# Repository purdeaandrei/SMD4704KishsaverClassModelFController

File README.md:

# SMD Model F controller based on TH Xwhatsit design. ('kishsaver' variant)

This variant is for IBM 4704 keyboards, aka 'kishsaver' class model F keyboards, like F107, F50, F62, F77
This variant is not 100% compatible with the https://www.modelfkeyboards.com/ recreations of the F62/F77, because the pin pitch is different,
although it is electrically compatible with those too, if one decides to wire it up with individual wires.

For other variants see:
* https://github.com/purdeaandrei/SMDModelFController/tree/extra_columns
* https://github.com/purdeaandrei/SMDModelFController
* https://github.com/listofoptions/TH-XWhatsIt

## Images

## Origins and license

This project is based on the Through-hole xwhatsit by listofoptions, which is un turn
based on the capsense controllers by XWhatsIt
(Tom Wong-Cornall). original liscencure holds, as well as CERN OSH
(compatible license).

original implementation of Tom Wong-Cornall's controller documented here

http://downloads.cornall.co/ibm-capsense-usb-web/ibm-capsense-usb.html

Working theory of operation is under the previous link.

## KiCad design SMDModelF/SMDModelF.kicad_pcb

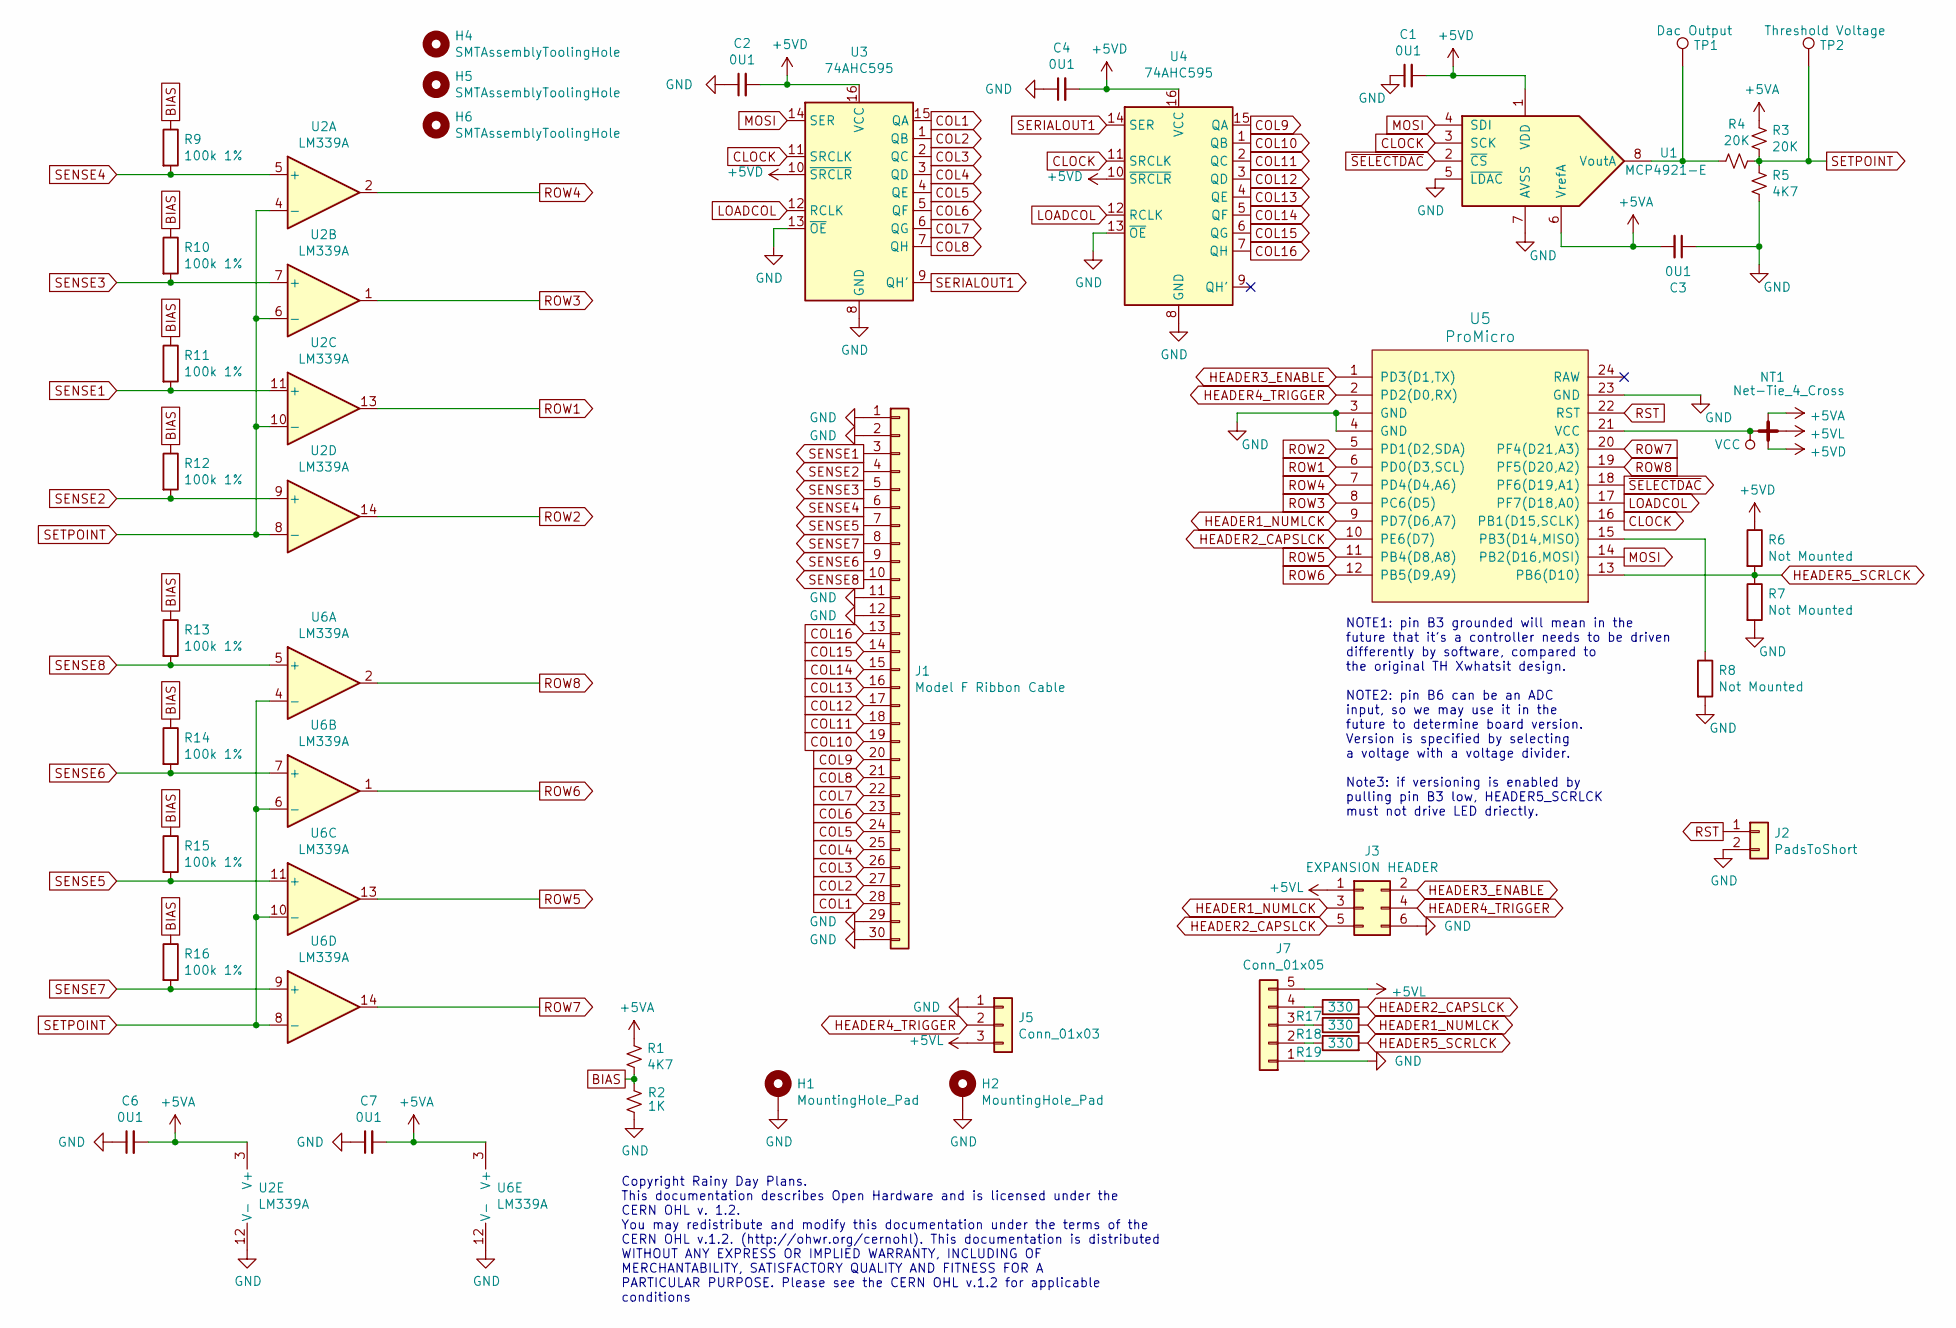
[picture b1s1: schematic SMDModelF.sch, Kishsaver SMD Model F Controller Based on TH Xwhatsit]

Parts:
C1, C2, C3, C4, C6, C7: 0U1; C_0805_2012Metric_Pad1.15x1.40mm_HandSolder; LCSC C49678
H1, H2: MountingHole_Pad; kishsaver_mounting_hole
H4, H5, H6: SMTAssemblyToolingHole; tooling_hole
J1: Model F Ribbon Cable; Model_F_3.96mm_pitch_footprint
J2: PadsToShort
J3: EXPANSION HEADER; SolenoidPinheaderNoCourtyard
J5: Conn_01x03; PinHeader_1x03_P2.54mm_Horizontal
J7: Conn_01x05; PinHeader_1x05_P2.54mm_Vertical_no3d
NT1: Net-Tie_4_Cross; NetTie-4_THT_Pad1.0mm
R1, R5: 4K7; R_0805_2012Metric_Pad1.15x1.40mm_HandSolder; LCSC C17673
R2: 1K; R_0805_2012Metric_Pad1.15x1.40mm_HandSolder; LCSC C17513
R3, R4: 20K; R_0805_2012Metric_Pad1.15x1.40mm_HandSolder; LCSC C4328
R6, R7, R8: Not Mounted; R_0805_2012Metric_Pad1.15x1.40mm_HandSolder
R9, R10, R11, R12, R13, R14, R15, R16: 100k 1%; R_0805_2012Metric_Pad1.15x1.40mm_HandSolder; LCSC C17407
R17, R18, R19: 330; R_0805_2012Metric_Pad1.15x1.40mm_HandSolder; LCSC C17630
TP1: Dac Output; TestPoint_Pad_D1.0mm
TP2: Threshold Voltage; TestPoint_Pad_D1.0mm
U1: MCP4921-E; SOIC-8_3.9x4.9mm_P1.27mm; LCSC C43499
U2, U6: LM339A; SOIC-14_3.9x8.7mm_P1.27mm; LCSC C74559
U3, U4: 74AHC595; SOIC-16_3.9x9.9mm_P1.27mm; LCSC C5520
U5: ProMicro

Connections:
+5VA: C3.2, C6.2, C7.2, NT1.3, R1.1, R3.2, U1.6 (VrefA), U2.3 (V+), U6.3 (V+)
+5VD: C1.2, C2.2, C4.2, NT1.4, R6.1, U1.1 (VDD), U3.10 (~SRCLR), U3.16 (VCC), U4.10 (~SRCLR), U4.16 (VCC)
+5VL: J3.1, J5.3, J7.5, NT1.2
BIAS: R1.2, R2.2, R9.1, R10.1, R11.1, R12.1, R13.1, R14.1, R15.1, R16.1
CLOCK: U1.3 (SCK), U3.11 (SRCLK), U4.11 (SRCLK), U5.16 (PB1(D15,SCLK))
COL1: J1.28, U3.15 (QA)
COL2: J1.27, U3.1 (QB)
COL3: J1.26, U3.2 (QC)
COL4: J1.25, U3.3 (QD)
COL5: J1.24, U3.4 (QE)
COL6: J1.23, U3.5 (QF)
COL7: J1.22, U3.6 (QG)
COL8: J1.21, U3.7 (QH)
COL9: J1.20, U4.15 (QA)
COL10: J1.19, U4.1 (QB)
COL11: J1.18, U4.2 (QC)
COL12: J1.17, U4.3 (QD)
COL13: J1.16, U4.4 (QE)
COL14: J1.15, U4.5 (QF)
COL15: J1.14, U4.6 (QG)
COL16: J1.13, U4.7 (QH)
GND: C1.1, C2.1, C3.1, C4.1, C6.1, C7.1, H1.1, H2.1, J1.1, J1.2, J1.11, J1.12, J1.29, J1.30, J2.2, J3.6, J5.1, J7.1, R2.1, R5.1, R7.2, R8.2, U1.5 (~LDAC~), U1.7 (AVSS), U2.12 (V-), U3.8 (GND), U3.13 (~OE), U4.8 (GND), U4.13 (~OE), U5.3 (GND), U5.4 (GND), U5.23 (GND), U6.12 (V-)
HEADER1_NUMLCK: J3.3, R18.2, U5.9 (PD7(D6,A7))
HEADER2_CAPSLCK: J3.5, R17.2, U5.10 (PE6(D7))
HEADER3_ENABLE: J3.2, U5.1 (PD3(D1,TX))
HEADER4_TRIGGER: J3.4, J5.2, U5.2 (PD2(D0,RX))
HEADER5_SCRLCK: R6.2, R7.1, R19.2, U5.13 (PB6(D10))
LOADCOL: U3.12 (RCLK), U4.12 (RCLK), U5.17 (PF7(D18,A0))
MOSI: U1.4 (SDI), U3.14 (SER), U5.14 (PB2(D16,MOSI))
unnamed: J7.2, R19.1
unnamed: J7.3, R18.1
unnamed: J7.4, R17.1
unnamed: R4.2, TP1.1, U1.8 (VoutA)
unnamed: R8.1, U5.15 (PB3(D14,MISO))
ROW1: U2.13, U5.6 (PD0(D3,SCL))
ROW2: U2.14, U5.5 (PD1(D2,SDA))
ROW3: U2.1, U5.8 (PC6(D5))
ROW4: U2.2, U5.7 (PD4(D4,A6))
ROW5: U5.11 (PB4(D8,A8)), U6.13
ROW6: U5.12 (PB5(D9,A9)), U6.1
ROW7: U5.20 (PF4(D21,A3)), U6.14
ROW8: U5.19 (PF5(D20,A2)), U6.2
RST: J2.1, U5.22 (RST)
SENSE1: J1.3, R11.2, U2.11 (+)
SENSE2: J1.4, R12.2, U2.9 (+)
SENSE3: J1.5, R10.2, U2.7 (+)
SENSE4: J1.6, R9.2, U2.5 (+)
SENSE5: J1.7, R15.2, U6.11 (+)
SENSE6: J1.9, R14.2, U6.7 (+)
SENSE7: J1.8, R16.2, U6.9 (+)
SENSE8: J1.10, R13.2, U6.5 (+)
SERIALOUT1: U3.9 (QH'), U4.14 (SER)
SETPOINT: R3.1, R4.1, R5.2, TP2.1, U2.4 (-), U2.6 (-), U2.8 (-), U2.10 (-), U6.4 (-), U6.6 (-), U6.8 (-), U6.10 (-)
VCC: NT1.1, U5.21 (VCC)
~SELECTDAC: U1.2 (~CS~), U5.18 (PF6(D19,A1))

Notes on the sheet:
Copyright Rainy Day Plans. This documentation describes Open Hardware and is licensed under the CERN OHL v. 1.2. You may redistribute and modify this documentation under the terms of the CERN OHL v.1.2. (http://ohwr.org/cernohl). This documentation is distributed WITHOUT ANY EXPRESS OR IMPLIED WARR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
NOTE1: pin B3 grounded will mean in the future that it's a controller needs to be driven differently by software, compared to the original TH Xwhatsit design. NOTE2: pin B6 can be an ADC input, so we may use it in the future to determine board version. Version is specified by selecting a voltage wi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

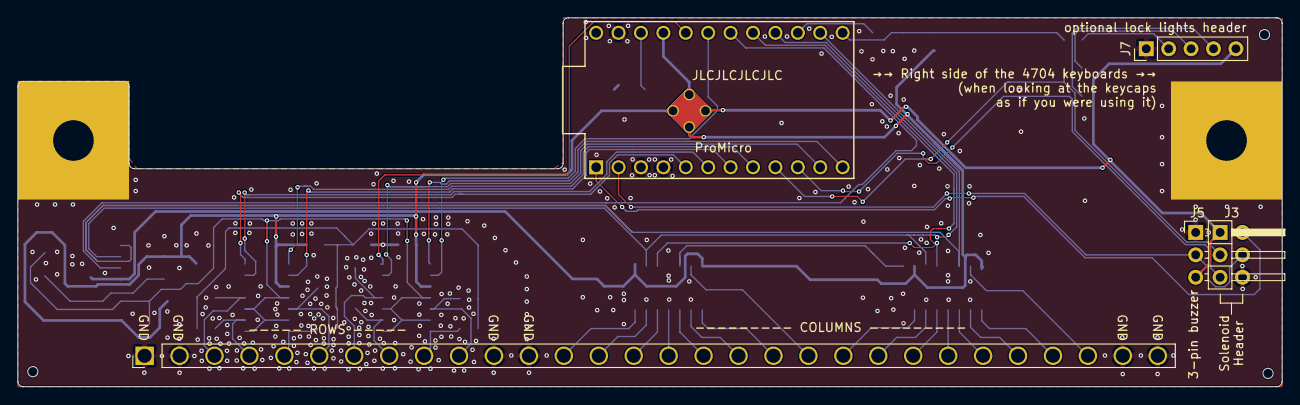
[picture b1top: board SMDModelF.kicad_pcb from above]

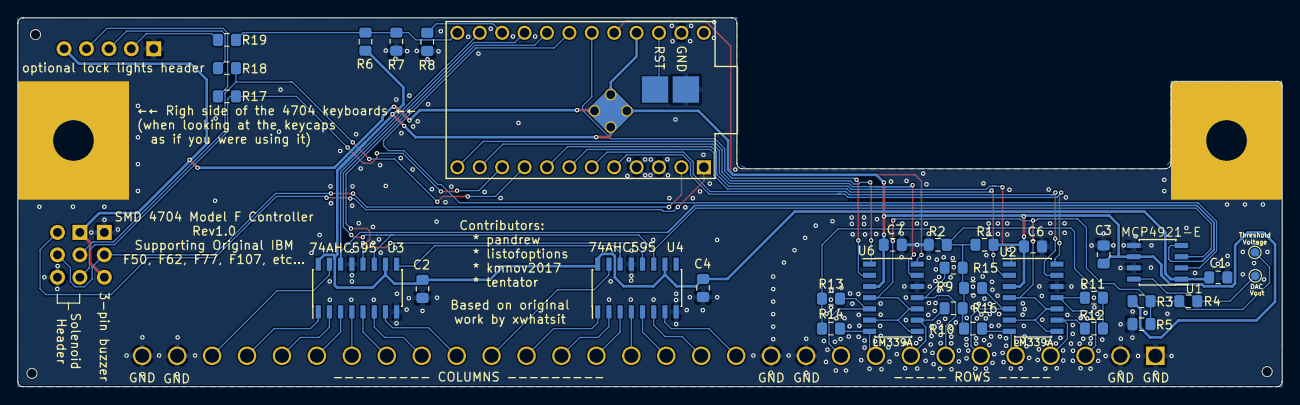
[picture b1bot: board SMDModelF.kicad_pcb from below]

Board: 2 copper layers, 143.3 x 41.8 mm, 44 parts (33 on the bottom side), 55 nets.

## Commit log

2020-09-30 First version of kishsaver-class model F controller
2020-12-13 Pro Micro footprint: updated to include 3d models by default.
2020-12-13 Added footprints for no-3d solenoid header, and with 3d for beeper header
2020-12-13 PCB file: updated footprints and references to 3d parts.
2021-05-03 Updated pro micro schematic symbol, and added PDF schematics
2021-10-30 Removed proprietary datasheets
2021-10-30 Clarify license of card edge model
2021-10-30 Clarified license of the footprint library
2021-10-30 Clarified the license of some more files
2021-10-30 Added another readme clarifying a license
2021-10-30 Updated Changes.txt
2021-10-30 Another update to licensing information
2021-10-30 Mark some components virtual, add images, tweak readme
2021-10-30 Fix up Readme
2022-02-14 Update component rotations, to match new behaviour of JLCPCB on the bottom layer
2022-07-31 Updated 100k resistor and shift register LCSC part numbers
2022-07-31 fix rotations to match latest JLCPCB behaviour
2022-09-15 Revert part of commit 'Updated 100k resistor and shift register LCSC part numbers' (the shift register BOM changes only)

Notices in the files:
SMDModelF/SMDModelF.kicad_pcb:
Licenced under CERN OHL Version 1.2
